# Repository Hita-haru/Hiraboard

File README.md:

# Hiraboard
This is a project of Blueprint which is in Hackclub's YSWS Program.
This is my first devboard.  
I made this devboard using this tutorial: https://blueprint.hackclub.com/starter-projects/devboard  

## PCB Screenshots  
Forward  

Backward  

## Schematic screenshot
  
## Estimates  

## Finished product

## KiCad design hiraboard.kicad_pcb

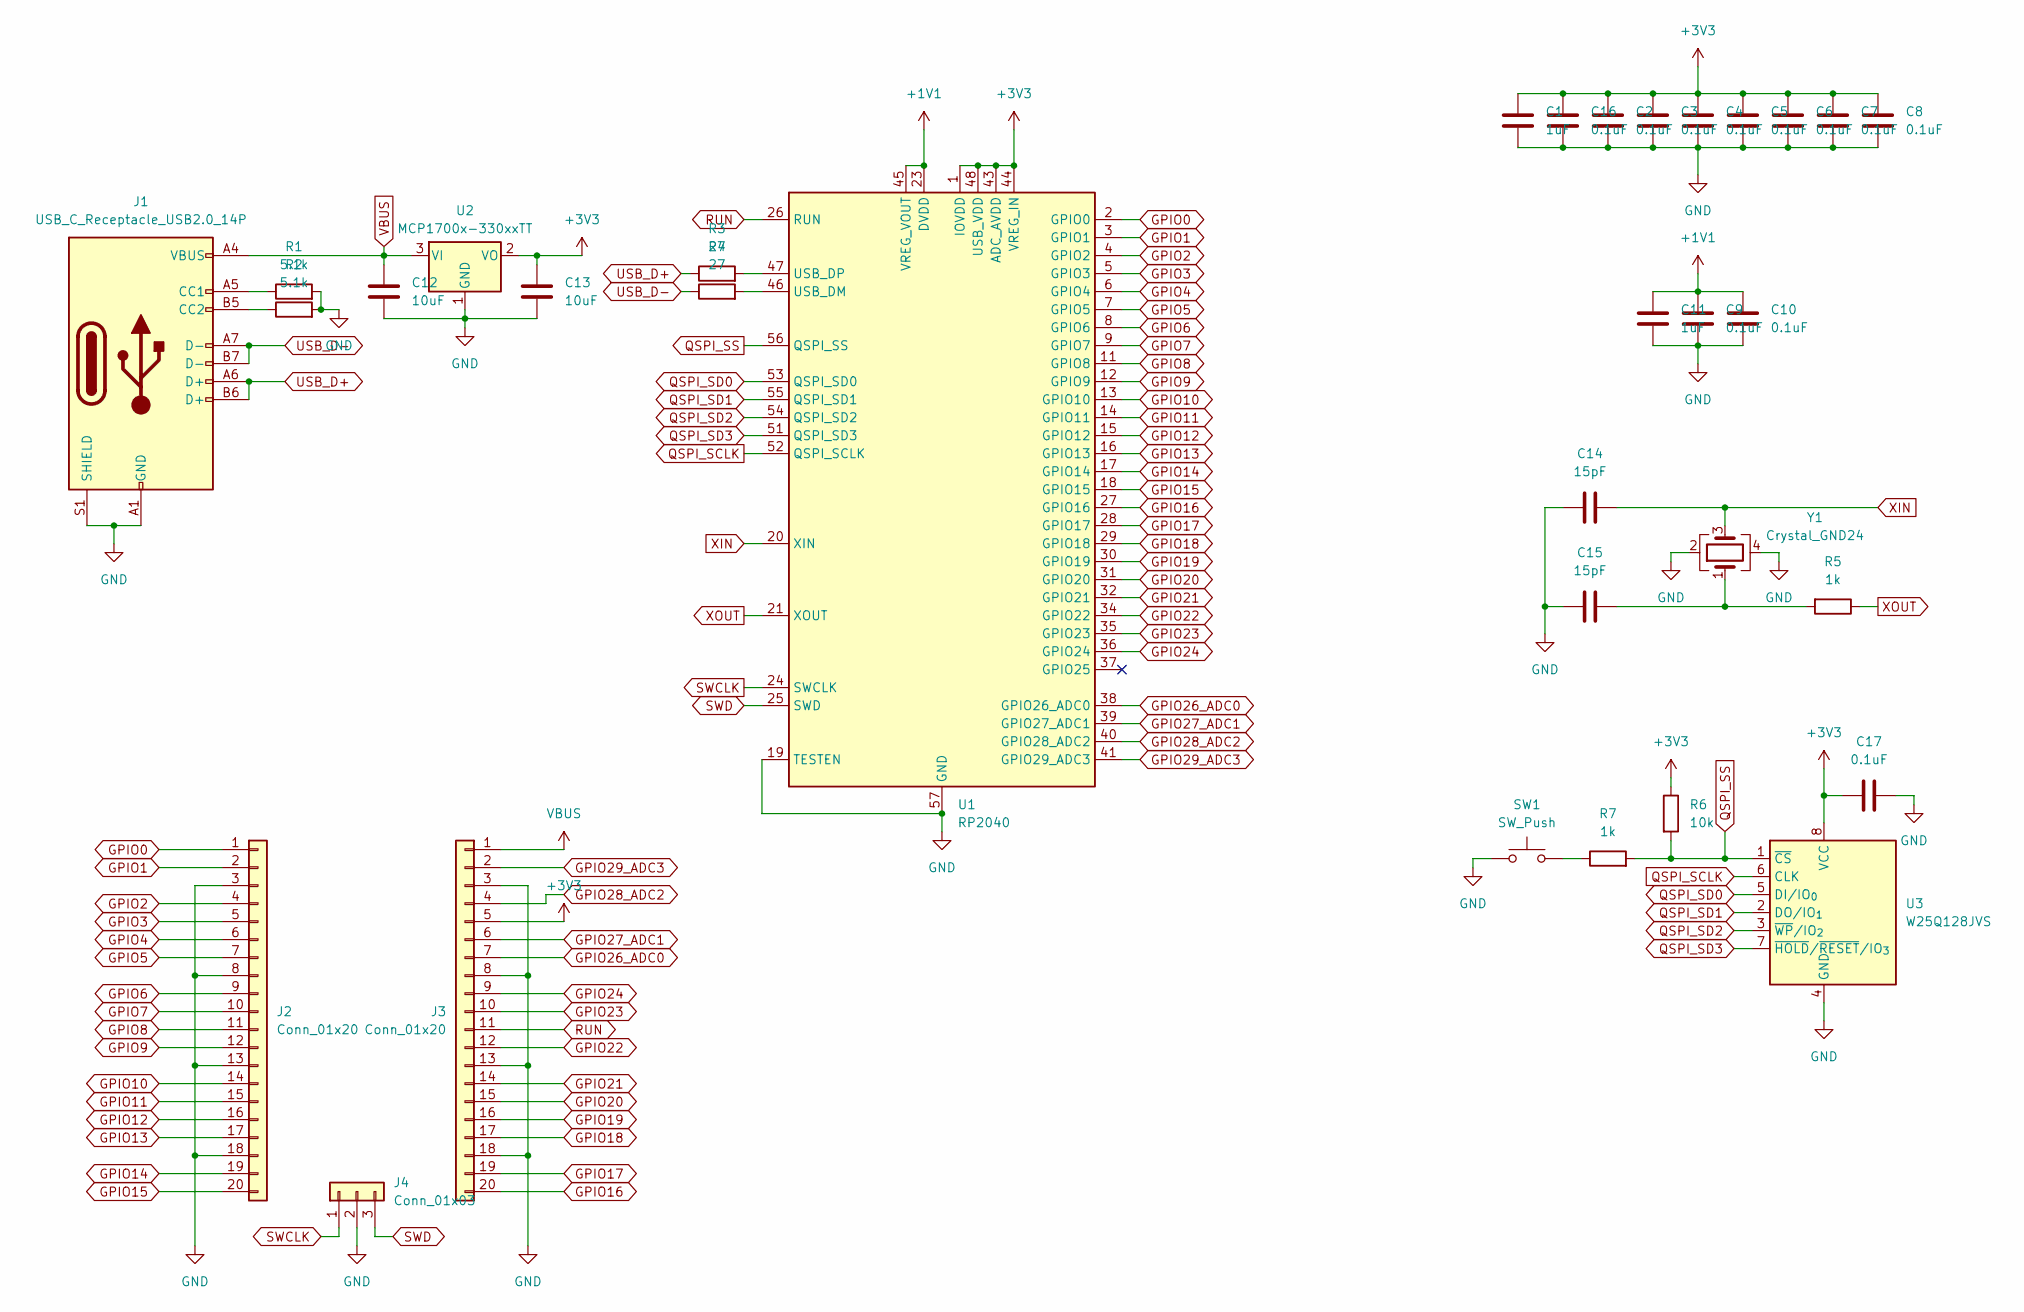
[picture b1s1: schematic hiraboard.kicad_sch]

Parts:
C1, C11: 1uF; C_0402_1005Metric
C2, C3, C4, C5, C6, C7, C8, C9, C10, C16, C17: 0.1uF; C_0402_1005Metric
C12, C13: 10uF; C_0603_1608Metric
C14, C15: 15pF; C_0402_1005Metric
J1: USB_C_Receptacle_USB2.0_14P; USB_C_Receptacle_HRO_TYPE-C-31-M-12
J2, J3: Conn_01x20; PinHeader_1x20_P2.54mm_Vertical
J4: Conn_01x03; PinHeader_1x03_P2.54mm_Vertical
R1, R2: 5.1k; R_0402_1005Metric
R3, R4: 27; R_0402_1005Metric
R5, R7: 1k; R_0402_1005Metric
R6: 10k; R_0402_1005Metric
SW1: SW_Push; SW_Push_SPST_NO_Alps_SKRK
U1: RP2040; QFN-56-1EP_7x7mm_P0.4mm_EP3.2x3.2mm
U2: MCP1700x-330xxTT; SOT-23
U3: W25Q128JVS; Winbond_USON-8-1EP_3x2mm_P0.5mm_EP0.2x1.6mm
Y1: Crystal_GND24; Crystal_SMD_3225-4Pin_3.2x2.5mm

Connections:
+1V1: C9.1, C10.1, C11.1, U1.23 (DVDD), U1.45 (VREG_VOUT), U1.50 (DVDD)
+3V3: C1.1, C2.1, C3.1, C4.1, C5.1, C6.1, C7.1, C8.1, C13.1, C16.1, C17.1, J3.5, R6.1, U1.1 (IOVDD), U1.10 (IOVDD), U1.22 (IOVDD), U1.33 (IOVDD), U1.42 (IOVDD), U1.43 (ADC_AVDD), U1.44 (VREG_IN), U1.48 (USB_VDD), U1.49 (IOVDD), U2.2 (VO), U3.8 (VCC)
GND: C1.2, C2.2, C3.2, C4.2, C5.2, C6.2, C7.2, C8.2, C9.2, C10.2, C11.2, C12.2, C13.2, C14.2, C15.2, C16.2, C17.2, J1.A1 (GND), J1.A12 (GND), J1.B1 (GND), J1.B12 (GND), J1.S1 (SHIELD), J2.3, J2.8, J2.13, J2.18, J3.3, J3.8, J3.13, J3.18, J4.2, R1.2, R2.2, SW1.1, U1.19 (TESTEN), U1.57 (GND), U2.1 (GND), U3.4 (GND), Y1.2, Y1.4
GPIO0: J2.1, U1.2 (GPIO0)
GPIO1: J2.2, U1.3 (GPIO1)
GPIO2: J2.4, U1.4 (GPIO2)
GPIO3: J2.5, U1.5 (GPIO3)
GPIO4: J2.6, U1.6 (GPIO4)
GPIO5: J2.7, U1.7 (GPIO5)
GPIO6: J2.9, U1.8 (GPIO6)
GPIO7: J2.10, U1.9 (GPIO7)
GPIO8: J2.11, U1.11 (GPIO8)
GPIO9: J2.12, U1.12 (GPIO9)
GPIO10: J2.14, U1.13 (GPIO10)
GPIO11: J2.15, U1.14 (GPIO11)
GPIO12: J2.16, U1.15 (GPIO12)
GPIO13: J2.17, U1.16 (GPIO13)
GPIO14: J2.19, U1.17 (GPIO14)
GPIO15: J2.20, U1.18 (GPIO15)
GPIO16: J3.20, U1.27 (GPIO16)
GPIO17: J3.19, U1.28 (GPIO17)
GPIO18: J3.17, U1.29 (GPIO18)
GPIO19: J3.16, U1.30 (GPIO19)
GPIO20: J3.15, U1.31 (GPIO20)
GPIO21: J3.14, U1.32 (GPIO21)
GPIO22: J3.12, U1.34 (GPIO22)
GPIO23: J3.10, U1.35 (GPIO23)
GPIO24: J3.9, U1.36 (GPIO24)
GPIO26_ADC0: J3.7, U1.38 (GPIO26_ADC0)
GPIO27_ADC1: J3.6, U1.39 (GPIO27_ADC1)
GPIO28_ADC2: J3.4, U1.40 (GPIO28_ADC2)
GPIO29_ADC3: J3.2, U1.41 (GPIO29_ADC3)
unnamed: C15.1, R5.2, Y1.1
unnamed: J1.A5 (CC1), R1.1
unnamed: J1.B5 (CC2), R2.1
unnamed: R7.1, SW1.2
unnamed: R4.2, U1.46 (USB_DM)
unnamed: R3.2, U1.47 (USB_DP)
unnamed: C12.1, J1.A4 (VBUS), J1.A9 (VBUS), J1.B4 (VBUS), J1.B9 (VBUS), U2.3 (VI)
QSPI_SCLK: U1.52 (QSPI_SCLK), U3.6 (CLK)
QSPI_SD0: U1.53 (QSPI_SD0), U3.5 (DI/IO_{0})
QSPI_SD1: U1.55 (QSPI_SD1), U3.2 (DO/IO_{1})
QSPI_SD2: U1.54 (QSPI_SD2), U3.3 (~WP/IO_{2})
QSPI_SD3: U1.51 (QSPI_SD3), U3.7 (~HOLD/~RESET/IO_{3})
QSPI_SS: R6.2, R7.2, U1.56 (QSPI_SS), U3.1 (~CS)
RUN: J3.11, U1.26 (RUN)
SWCLK: J4.1, U1.24 (SWCLK)
SWD: J4.3, U1.25 (SWD)
USB_D+: J1.A6 (D+), J1.B6 (D+), R3.1
USB_D-: J1.A7 (D-), J1.B7 (D-), R4.1
VBUS: J3.1
XIN: C14.1, U1.20 (XIN), Y1.3
XOUT: R5.1, U1.21 (XOUT)

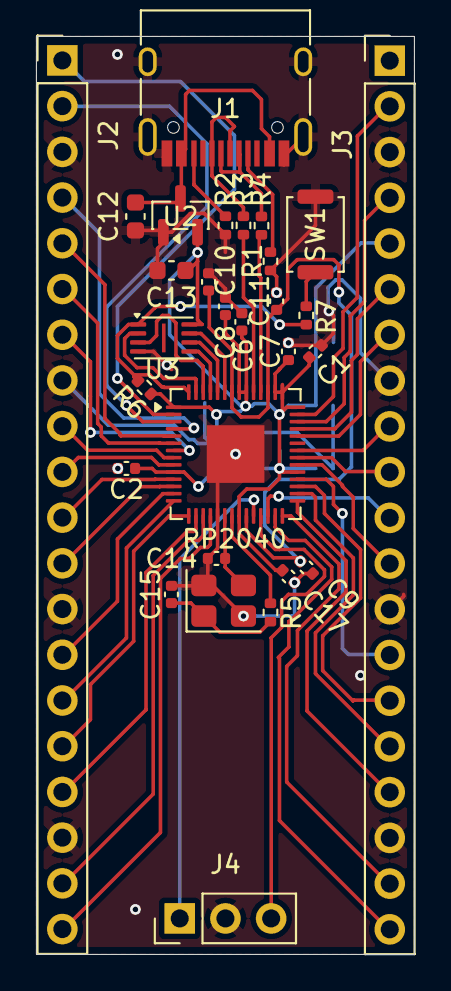
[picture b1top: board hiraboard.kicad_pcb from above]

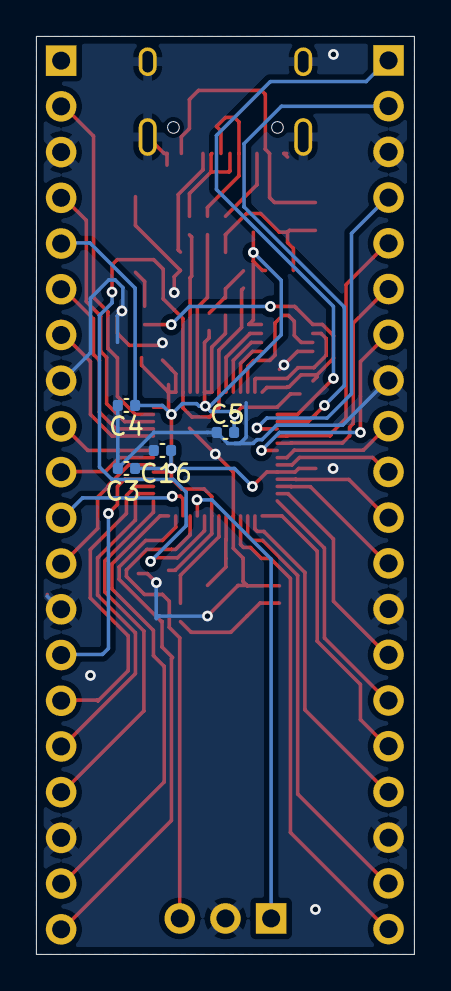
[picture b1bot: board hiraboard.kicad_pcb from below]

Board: 2 copper layers, 21.0 x 51.0 mm, 33 parts (4 on the bottom side), 52 nets.

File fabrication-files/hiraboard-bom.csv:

ID,Designator,Footprint,Quantity,Comment,供給業者、参考資料
1,"C15,C14",C_0402_1005Metric,2,15pF,
2,"R7,R5",R_0402_1005Metric,2,1k,
3,U2,SOT-23,1,MCP1700x-330xxTT,
4,"C10,C8,C17,C7,C6,C9,C2,C4,C5,C3,C16",C_0402_1005Metric,11,0.1uF,
5,Y1,Crystal_SMD_3225-4Pin_3.2x2.5mm,1,Crystal_GND24,
6,U1,QFN-56-1EP_7x7mm_P0.4mm_EP3.2x3.2mm,1,RP2040,
7,"J3,J2",PinHeader_1x20_P2.54mm_Vertical,2,Conn_01x20,
8,"R4,R3",R_0402_1005Metric,2,27,
9,SW1,SW_Push_SPST_NO_Alps_SKRK,1,SW_Push,
10,R6,R_0402_1005Metric,1,10k,
11,"C1,C11",C_0402_1005Metric,2,1uF,
12,J4,PinHeader_1x03_P2.54mm_Vertical,1,Conn_01x03,
13,"C12,C13",C_0603_1608Metric,2,10uF,
14,J1,USB_C_Receptacle_HRO_TYPE-C-31-M-12,1,USB_C_Receptacle_USB2.0_14P,
15,U3,Winbond_USON-8-1EP_3x2mm_P0.5mm_EP0.2x1.6mm,1,W25Q128JVS,
16,"R2,R1",R_0402_1005Metric,2,5.1k,

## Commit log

2025-11-26 Add any files
2025-11-30 Add PCB images
2025-11-30 Add Schematic PDF
2025-11-30 Add initial README for Hiraboard project
2025-11-30 Add JLCPCB estimate screen shot
2025-11-30 Add Digikey estimate
2025-11-30 File Organization
2025-12-01 Edit README
2025-12-02 Update estimate
2025-12-11 Add schematic screenshot section to README
2025-12-11 Add shipping options image to README
2026-02-24 Add finished product section to README
    Added a section for the finished product with an image.
2026-02-24 Fix image syntax in README for finished product
2026-02-24 Update image format for finished product screenshot
